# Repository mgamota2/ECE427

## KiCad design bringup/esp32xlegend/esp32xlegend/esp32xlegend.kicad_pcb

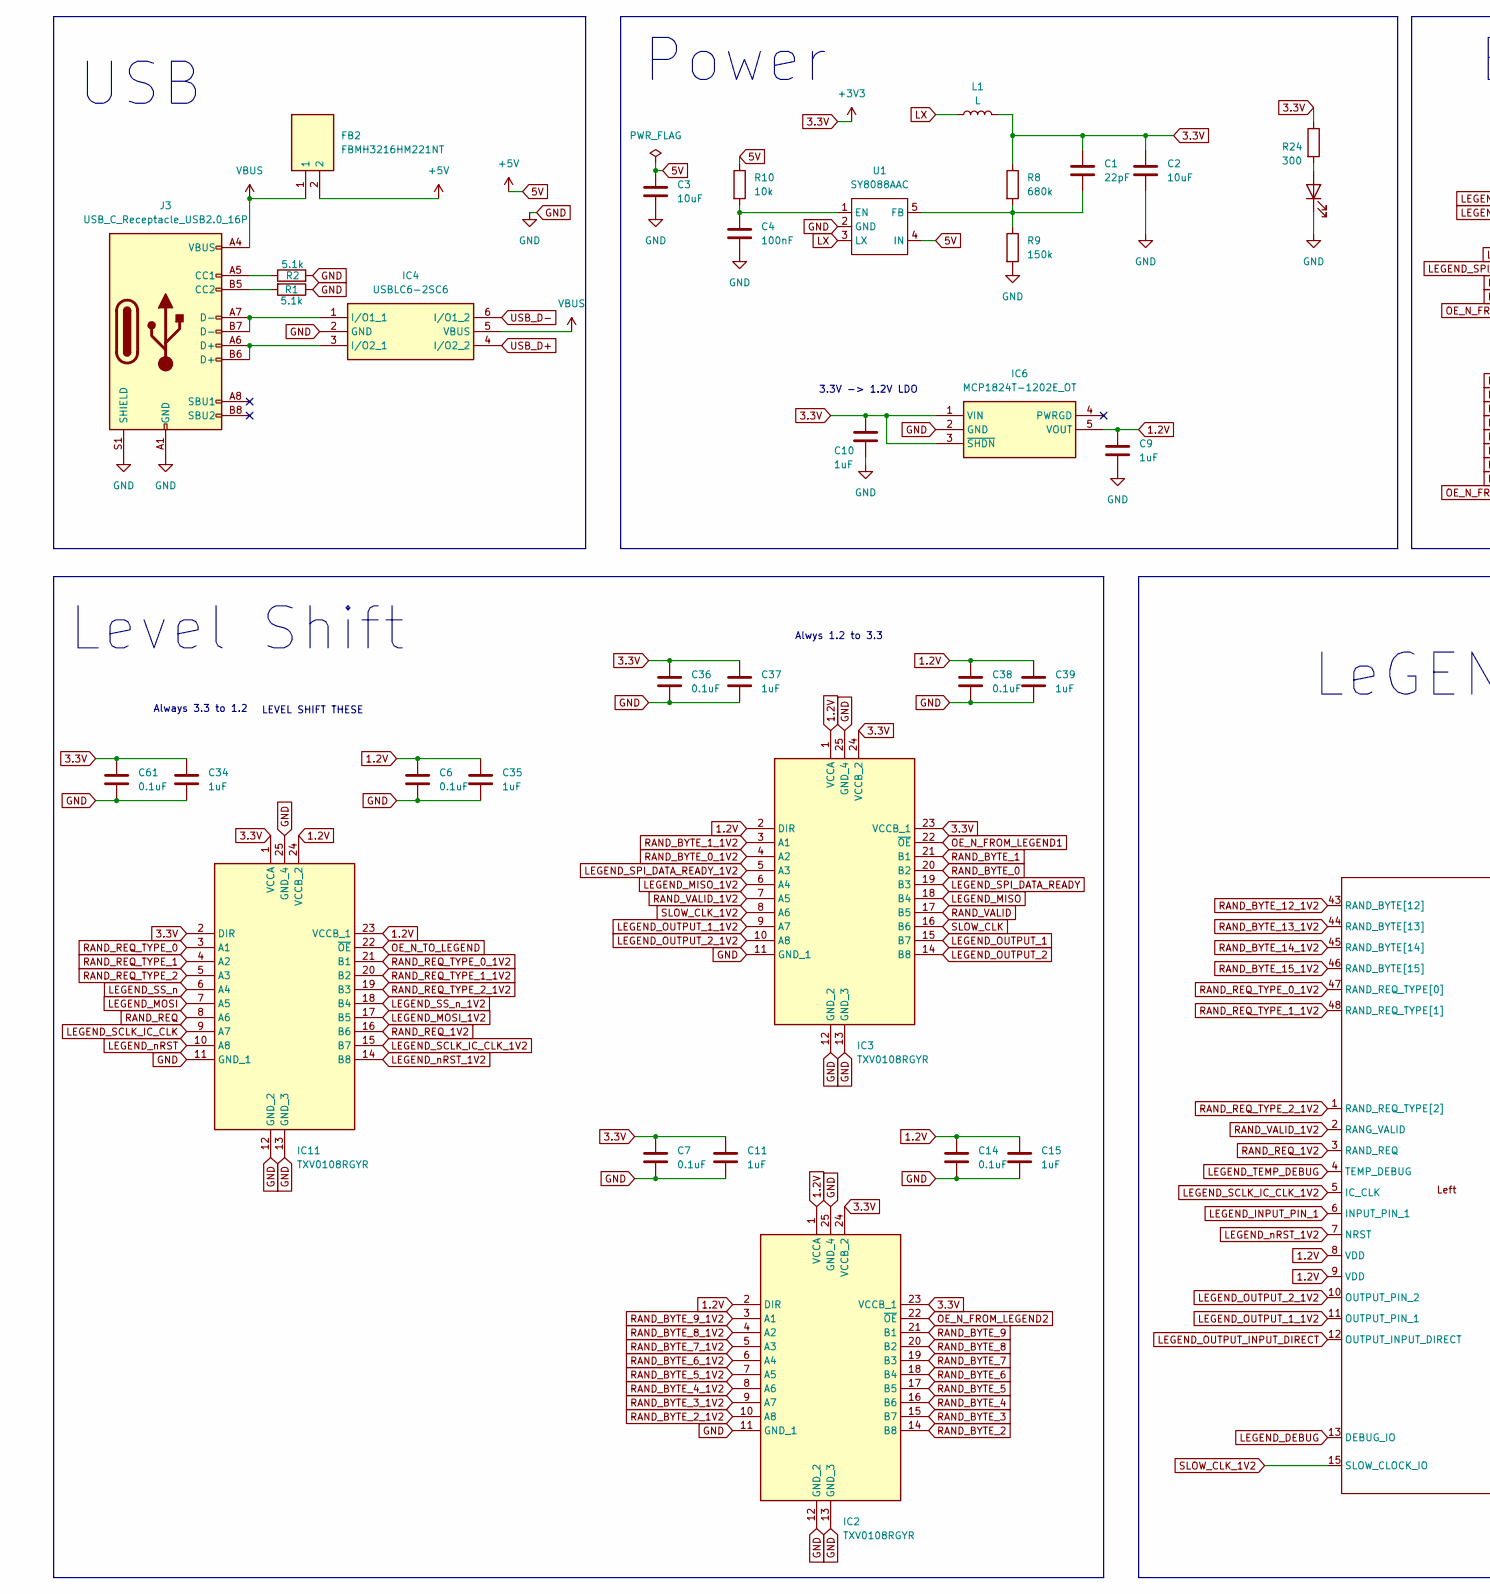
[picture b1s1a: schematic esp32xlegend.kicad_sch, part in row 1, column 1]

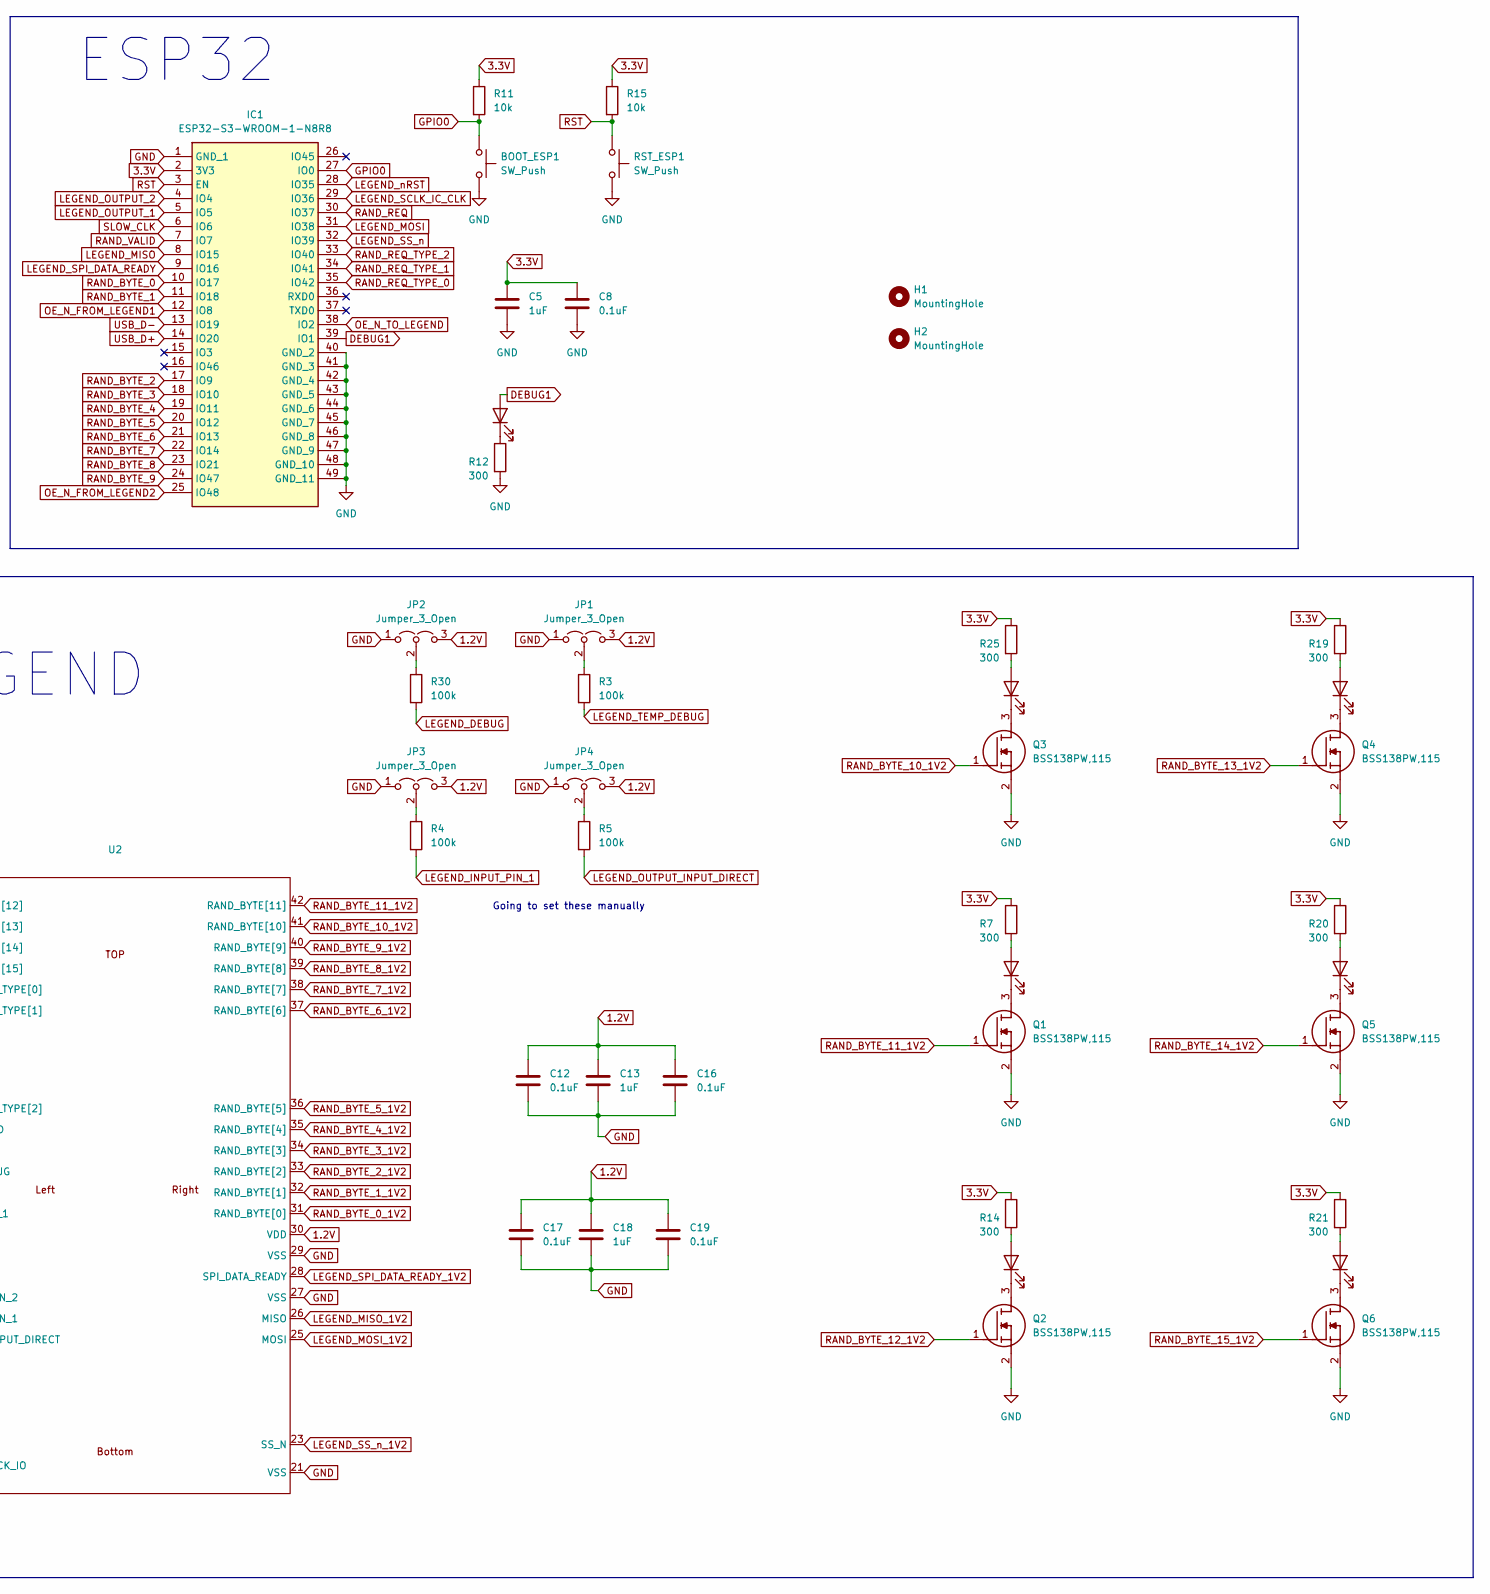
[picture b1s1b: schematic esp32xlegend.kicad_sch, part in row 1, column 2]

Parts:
3V3_1: LED; LED_0603_1608Metric
BOOT_ESP1: SW_Push; B3U1000PM
C1: 22pF; C_0603_1608Metric
C2, C3: 10uF; C_0603_1608Metric
C4: 100nF; C_0402_1005Metric
C5, C13, C18: 1uF; C_0603_1608Metric
C6, C7, C14, C36, C38, C61: 0.1uF; C_0402_1005Metric
C8, C12, C16, C17, C19: 0.1uF; C_0603_1608Metric
C9, C10, C11, C15, C34, C35, C37, C39: 1uF; C_0402_1005Metric
DEBUG3: LED; LED_0603_1608Metric
FB2: FBMH3216HM221NT; BEADC3216X180N; Mouser Part Number 963-FBMH3216HM221NT
H1, H2: MountingHole; MountingHole_2.2mm_M2
IC1: ESP32-S3-WROOM-1-N8R8; ESP32S3WROOM1N8R8; Mouser Part Number 356-EP32S3WROOM1N8R8
IC2, IC3, IC11: TXV0108RGYR; Mouser Part Number 595-TXV0108RGYR
IC4: USBLC6-2SC6; SOT95P280X145-6N; Mouser Part Number 511-USBLC6-2SC6
IC6: MCP1824T-1202E_OT; SOT95P270X145-5N; Mouser Part Number 579-MCP1824T-1202EOT
J3: USB_C_Receptacle_USB2.0_16P; USB_C_Receptacle_GCT_USB4085
JP1, JP2, JP3, JP4: Jumper_3_Open; SolderJumper-3_P1.3mm_Open_Pad1.0x1.5mm
L1: L; L_1008_2520Metric
Q1, Q2, Q3, Q4, Q5, Q6: BSS138PW,115; SOT65P210X110-3N; Mouser Part Number 771-BSS138PW115
R1, R2: 5.1k; R_0402_1005Metric
R3, R4, R5, R30: 100k; R_0402_1005Metric
R7, R12, R14, R19, R20, R21, R24, R25: 300; R_0402_1005Metric
R8: 680k; R_0603_1608Metric
R9: 150k; R_0603_1608Metric
R10: 10k; R_0603_1608Metric
R11, R15: 10k; R_0402_1005Metric
RAND10, RAND11, RAND12, RAND13, RAND14, RAND15: LED; LED_0603_1608Metric
RST_ESP1: SW_Push; B3U1000PM
U1: SY8088AAC; SOT-23-5_HandSoldering
U2: CHIP

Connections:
1.2V: C6.1, C9.1, C12.1, C13.1, C14.1, C15.1, C16.1, C17.1, C18.1, C19.1, C35.1, C38.1, C39.1, IC2.1 (VCCA), IC2.2 (DIR), IC3.1 (VCCA), IC3.2 (DIR), IC6.5 (VOUT), IC11.23 (VCCB_1), IC11.24 (VCCB_2), JP1.3 (B), JP2.3 (B), JP3.3 (B), JP4.3 (B), U2.8 (VDD), U2.9 (VDD), U2.30 (VDD)
3.3V: C1.1, C2.1, C5.1, C7.1, C8.1, C10.1, C11.1, C34.1, C36.1, C37.1, C61.1, IC1.2 (3V3), IC2.23 (VCCB_1), IC2.24 (VCCB_2), IC3.23 (VCCB_1), IC3.24 (VCCB_2), IC6.1 (VIN), IC6.3 (~SHDN), IC11.1 (VCCA), IC11.2 (DIR), L1.2, R7.1, R8.1, R11.1, R14.1, R15.1, R19.1, R20.1, R21.1, R24.1, R25.1
5V: C3.1, FB2.2, R10.1, U1.4 (IN)
DEBUG1: DEBUG3.2 (A), IC1.39 (IO1)
GND: 3V3_1.1 (K), BOOT_ESP1.2, C2.2, C3.2, C4.2, C5.2, C6.2, C7.2, C8.2, C9.2, C10.2, C11.2, C12.2, C13.2, C14.2, C15.2, C16.2, C17.2, C18.2, C19.2, C34.2, C35.2, C36.2, C37.2, C38.2, C39.2, C61.2, IC1.1 (GND_1), IC1.40 (GND_2), IC1.41 (GND_3), IC1.42 (GND_4), IC1.43 (GND_5), IC1.44 (GND_6), IC1.45 (GND_7), IC1.46 (GND_8), IC1.47 (GND_9), IC1.48 (GND_10), IC1.49 (GND_11), IC2.11 (GND_1), IC2.12 (GND_2), IC2.13 (GND_3), IC2.25 (GND_4), IC3.11 (GND_1), IC3.12 (GND_2), IC3.13 (GND_3), IC3.25 (GND_4), IC4.2 (GND), IC6.2 (GND), IC11.11 (GND_1), IC11.12 (GND_2), IC11.13 (GND_3), IC11.25 (GND_4), J3.A1 (GND), J3.A12 (GND), J3.B1 (GND), J3.B12 (GND), J3.S1 (SHIELD), JP1.1 (A), JP2.1 (A), JP3.1 (A), JP4.1 (A), Q1.2 (S), Q2.2 (S), Q3.2 (S), Q4.2 (S), Q5.2 (S), Q6.2 (S), R1.1, R2.2, R9.2, R12.2, RST_ESP1.2, U1.2 (GND), U2.21 (VSS), U2.27 (VSS), U2.29 (VSS)
GPIO0: BOOT_ESP1.1, IC1.27 (IO0), R11.2
LEGEND_DEBUG: R30.2, U2.13 (DEBUG_IO)
LEGEND_INPUT_PIN_1: R4.2, U2.6 (INPUT_PIN_1)
LEGEND_MISO: IC1.8 (IO15), IC3.18 (B4)
LEGEND_MISO_1V2: IC3.6 (A4), U2.26 (MISO)
LEGEND_MOSI: IC1.31 (IO38), IC11.7 (A5)
LEGEND_MOSI_1V2: IC11.17 (B5), U2.25 (MOSI)
LEGEND_OUTPUT_1: IC1.5 (IO5), IC3.15 (B7)
LEGEND_OUTPUT_1_1V2: IC3.9 (A7), U2.11 (OUTPUT_PIN_1)
LEGEND_OUTPUT_2: IC1.4 (IO4), IC3.14 (B8)
LEGEND_OUTPUT_2_1V2: IC3.10 (A8), U2.10 (OUTPUT_PIN_2)
LEGEND_OUTPUT_INPUT_DIRECT: R5.2, U2.12 (OUTPUT_INPUT_DIRECT)
LEGEND_SCLK_IC_CLK: IC1.29 (IO36), IC11.9 (A7)
LEGEND_SCLK_IC_CLK_1V2: IC11.15 (B7), U2.5 (IC_CLK)
LEGEND_SPI_DATA_READY: IC1.9 (IO16), IC3.19 (B3)
LEGEND_SPI_DATA_READY_1V2: IC3.5 (A3), U2.28 (SPI_DATA_READY)
LEGEND_SS_n: IC1.32 (IO39), IC11.6 (A4)
LEGEND_SS_n_1V2: IC11.18 (B4), U2.23 (SS_N)
LEGEND_TEMP_DEBUG: R3.2, U2.4 (TEMP_DEBUG)
LEGEND_nRST: IC1.28 (IO35), IC11.10 (A8)
LEGEND_nRST_1V2: IC11.14 (B8), U2.7 (NRST)
LX: L1.1, U1.3 (LX)
unnamed: 3V3_1.2 (A), R24.2
unnamed: DEBUG3.1 (K), R12.1
unnamed: IC4.1 (I/O1_1), J3.A7 (D-), J3.B7 (D-)
unnamed: IC4.3 (I/O2_1), J3.A6 (D+), J3.B6 (D+)
unnamed: J3.A5 (CC1), R2.1
unnamed: J3.B5 (CC2), R1.2
unnamed: JP1.2 (C), R3.1
unnamed: JP2.2 (C), R30.1
unnamed: JP3.2 (C), R4.1
unnamed: JP4.2 (C), R5.1
unnamed: Q1.3 (D), RAND11.1 (K)
unnamed: Q2.3 (D), RAND12.1 (K)
unnamed: Q3.3 (D), RAND10.1 (K)
unnamed: Q4.3 (D), RAND13.1 (K)
unnamed: Q5.3 (D), RAND14.1 (K)
unnamed: Q6.3 (D), RAND15.1 (K)
unnamed: R25.2, RAND10.2 (A)
unnamed: R7.2, RAND11.2 (A)
unnamed: R14.2, RAND12.2 (A)
unnamed: R19.2, RAND13.2 (A)
unnamed: R20.2, RAND14.2 (A)
unnamed: R21.2, RAND15.2 (A)
unnamed: C4.1, R10.2, U1.1 (EN)
unnamed: C1.2, R8.2, R9.1, U1.5 (FB)
OE_N_FROM_LEGEND1: IC1.12 (IO8), IC3.22 (~OE)
OE_N_FROM_LEGEND2: IC1.25 (IO48), IC2.22 (~OE)
OE_N_TO_LEGEND: IC1.38 (IO2), IC11.22 (~OE)
RAND_BYTE_0: IC1.10 (IO17), IC3.20 (B2)
RAND_BYTE_0_1V2: IC3.4 (A2), U2.31 (RAND_BYTE[0])
RAND_BYTE_1: IC1.11 (IO18), IC3.21 (B1)
RAND_BYTE_1_1V2: IC3.3 (A1), U2.32 (RAND_BYTE[1])
RAND_BYTE_2: IC1.17 (IO9), IC2.14 (B8)
RAND_BYTE_2_1V2: IC2.10 (A8), U2.33 (RAND_BYTE[2])
RAND_BYTE_3: IC1.18 (IO10), IC2.15 (B7)
RAND_BYTE_3_1V2: IC2.9 (A7), U2.34 (RAND_BYTE[3])
RAND_BYTE_4: IC1.19 (IO11), IC2.16 (B6)
RAND_BYTE_4_1V2: IC2.8 (A6), U2.35 (RAND_BYTE[4])
RAND_BYTE_5: IC1.20 (IO12), IC2.17 (B5)
RAND_BYTE_5_1V2: IC2.7 (A5), U2.36 (RAND_BYTE[5])
RAND_BYTE_6: IC1.21 (IO13), IC2.18 (B4)
RAND_BYTE_6_1V2: IC2.6 (A4), U2.37 (RAND_BYTE[6])
RAND_BYTE_7: IC1.22 (IO14), IC2.19 (B3)
RAND_BYTE_7_1V2: IC2.5 (A3), U2.38 (RAND_BYTE[7])
RAND_BYTE_8: IC1.23 (IO21), IC2.20 (B2)
RAND_BYTE_8_1V2: IC2.4 (A2), U2.39 (RAND_BYTE[8])
RAND_BYTE_9: IC1.24 (IO47), IC2.21 (B1)
RAND_BYTE_9_1V2: IC2.3 (A1), U2.40 (RAND_BYTE[9])
RAND_BYTE_10_1V2: Q3.1 (G), U2.41 (RAND_BYTE[10])
RAND_BYTE_11_1V2: Q1.1 (G), U2.42 (RAND_BYTE[11])
RAND_BYTE_12_1V2: Q2.1 (G), U2.43 (RAND_BYTE[12])
RAND_BYTE_13_1V2: Q4.1 (G), U2.44 (RAND_BYTE[13])
RAND_BYTE_14_1V2: Q5.1 (G), U2.45 (RAND_BYTE[14])
RAND_BYTE_15_1V2: Q6.1 (G), U2.46 (RAND_BYTE[15])
RAND_REQ: IC1.30 (IO37), IC11.8 (A6)
RAND_REQ_1V2: IC11.16 (B6), U2.3 (RAND_REQ)
RAND_REQ_TYPE_0: IC1.35 (IO42), IC11.3 (A1)
RAND_REQ_TYPE_0_1V2: IC11.21 (B1), U2.47 (RAND_REQ_TYPE[0])
RAND_REQ_TYPE_1: IC1.34 (IO41), IC11.4 (A2)
RAND_REQ_TYPE_1_1V2: IC11.20 (B2), U2.48 (RAND_REQ_TYPE[1])
RAND_REQ_TYPE_2: IC1.33 (IO40), IC11.5 (A3)
RAND_REQ_TYPE_2_1V2: IC11.19 (B3), U2.1 (RAND_REQ_TYPE[2])
RAND_VALID: IC1.7 (IO7), IC3.17 (B5)
RAND_VALID_1V2: IC3.7 (A5), U2.2 (RANG_VALID)
RST: IC1.3 (EN), R15.2, RST_ESP1.1
SLOW_CLK: IC1.6 (IO6), IC3.16 (B6)
SLOW_CLK_1V2: IC3.8 (A6), U2.15 (SLOW_CLOCK_IO)
USB_D+: IC1.14 (IO20), IC4.4 (I/O2_2)
USB_D-: IC1.13 (IO19), IC4.6 (I/O1_2)
VBUS: FB2.1, IC4.5 (VBUS), J3.A4 (VBUS), J3.A9 (VBUS), J3.B4 (VBUS), J3.B9 (VBUS)

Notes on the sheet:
3.3V -> 1.2V LDO
Power
ESP32
LEVEL SHIFT THESE
Level Shift
Going to set these manually
USB
Alwys 1.2 to 3.3
Always 3.3 to 1.2
LeGEND

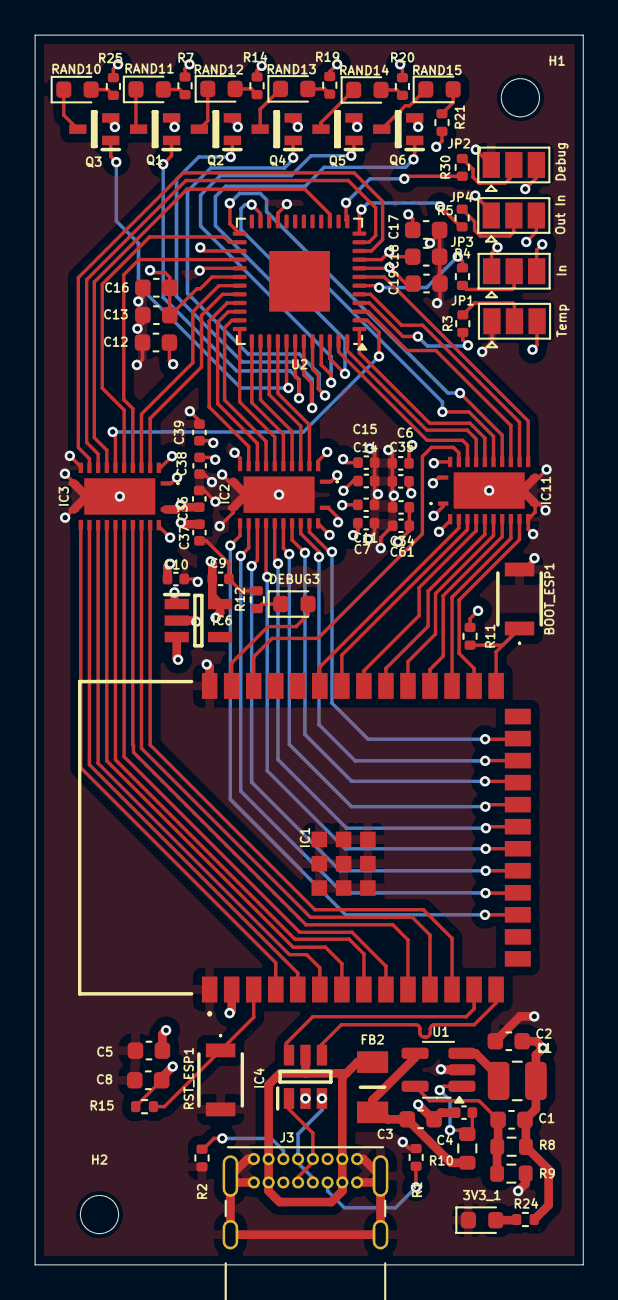
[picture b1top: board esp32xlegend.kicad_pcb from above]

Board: 4 copper layers, 31.6 x 70.9 mm, 78 parts (0 on the bottom side), 96 nets.

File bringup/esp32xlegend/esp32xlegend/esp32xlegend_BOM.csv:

Reference,Value,Datasheet,Footprint,Qty,DNP,JLCPCB #
"3V3_1,DEBUG3,RAND10,RAND11,RAND12,RAND13,RAND14,RAND15",LED,~,LED_SMD:LED_0603_1608Metric,8,,C72041
"BOOT_ESP1,RST_ESP1",SW_Push,~,SamacSys_Parts:B3U1000PM,2,,C231329
C1,22pF,~,Capacitor_SMD:C_0603_1608Metric,1,,C1653
"C2,C3",10uF,~,Capacitor_SMD:C_0603_1608Metric,2,,C1691
C4,100nF,~,Capacitor_SMD:C_0402_1005Metric,1,,C1525
"C5,C13,C18",1uF,~,Capacitor_SMD:C_0603_1608Metric,3,,C1592
"C6,C7,C14,C36,C38,C61",0.1uF,~,Capacitor_SMD:C_0402_1005Metric,6,,C1525
"C8,C12,C16,C17,C19",0.1uF,~,Capacitor_SMD:C_0603_1608Metric,5,,C1590
"C9,C10,C11,C15,C34,C35,C37,C39",1uF,~,Capacitor_SMD:C_0402_1005Metric,8,,C14445
FB2,FBMH3216HM221NT,https://ds.yuden.co.jp/TYCOMPAS/ut/detail?pn=FBMH3216HM221NT &u=M,SamacSys_Parts:BEADC3216X180N,1,,C7217634
IC1,ESP32-S3-WROOM-1-N8R8,https://www.espressif.com/sites/default/files/documentation/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,SamacSys_Parts:ESP32S3WROOM1N8R8,1,,C2913201
"IC2,IC3,IC11",TXV0108RGYR,https://www.ti.com/lit/ds/symlink/txv0108.pdf?ts=17104185317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,SamacSys_Parts:TXV0108RGYR,3,,C22428389
IC4,USBLC6-2SC6,http://www.st.com/st-web-ui/static/active/en/resource/techni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,SamacSys_Parts:SOT95P280X145-6N,1,,C7519
IC6,MCP1824T-1202E_OT,https://ww1.microchip.com/downloads/en/DeviceDoc/22070a.pdf,SamacSys_Parts:SOT95P270X145-5N,1,,C625461
J3,USB_C_Receptacle_USB2.0_16P,https://www.usb.org/sites/default/files/documents/usb_type-c.zip,Connector_USB:USB_C_Receptacle_GCT_USB4085,1,,C36936564
L1,L,~,Inductor_SMD:L_1008_2520Metric,1,,C23894
"Q1,Q2,Q3,Q4,Q5,Q6","BSS138PW,115",https://assets.nexperia.com/documents/data-sheet/BSS138PW.pdf,SamacSys_Parts:SOT65P210X110-3N,6,,C193366
"R1,R2",5.1k,~,Resistor_SMD:R_0402_1005Metric,2,,C25905
"R3,R4,R5,R30",100k,~,Resistor_SMD:R_0402_1005Metric,4,,C25530
"R7,R12,R14,R19,R20,R21,R24,R25",300,~,Resistor_SMD:R_0402_1005Metric,8,,C25102
R8,680k,~,Resistor_SMD:R_0603_1608Metric,1,,C25822
R9,150k,~,Resistor_SMD:R_0603_1608Metric,1,,C22807
R10,10k,~,Resistor_SMD:R_0603_1608Metric,1,,C15401
"R11,R15",10k,~,Resistor_SMD:R_0402_1005Metric,2,,C25531
U1,SY8088AAC,,Package_TO_SOT_SMD:SOT-23-5_HandSoldering,1,,C79313
U2,~,,LEGEND:CHIP,1,DNP,

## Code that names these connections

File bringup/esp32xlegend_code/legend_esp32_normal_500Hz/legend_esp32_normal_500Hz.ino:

// LEGEND is a custom random number generator ASIC. It has a debug mode and a default mode. In debug
// mode, the user can test submodules and route external inputs (INPUT pin) to intermediate submodules and route
// internal signals to the OUTPUT1 and OUTPUT 2 pins. In default mode, the RAND_REQ_TYPE pins are configured
// to request a 16, 32, or 64 bit RDSEED or RDRAND. Rand req must go high to submit the request. The output is
// sampled from the RAND_BYTE [0:15] pins, only [0:9] is sent to the ESP32 S3 WROOM. LEGEND operates at 1.2V
// so level shifters are used for all inputs and outputs. These level shifters are enabled with "OE_N_TO_LEGEND", 
// "OE_N_FROM_LEGEND1" and "OE_N_FROM_LEGEND2". Output bits in default mode are sampled when RAND_VALID is high
// and the bits are updated on the rising edge of SLOW_CLK.
// In debug mode, the CLK pin is used as the SPI clock to interface with a custom 22-bit message SPI interface. 
// All commands are register reads or writes, but write commands that write to the "debug state register" are treated
// specially as "Mux configuration commands". These commands select which submodules the output and input pins connect to.

#define LEGEND_OUTPUT_2 4
#define LEGEND_OUTPUT_1 5
#define LEGEND_SLOW_CLK 6
#define RAND_VALID 7
#define LEGEND_MISO 15
#define LEGEND_SPI_DATA_READY 16
#define RAND_BYTE_0 17
#define RAND_BYTE_1 18
#define OE_N_FROM_LEGEND_1 8
#define RAND_BYTE_2 9
#define RAND_BYTE_3 10
#define RAND_BYTE_4 11
#define RAND_BYTE_5 12
#define RAND_BYTE_6 13
#define RAND_BYTE_7 14
#define RAND_BYTE_8 21
#define RAND_BYTE_9 47
#define OE_N_FROM_LEGEND_2 48
#define LEGEND_nRST 35
#define LEGEND_SCLK_IC_CLK 36
#define RAND_REQ 37
#define LEGEND_MOSI 38
#define LEGEND_SS_n 39
#define RAND_REQ_TYPE_2 40
#define RAND_REQ_TYPE_1 41
#define RAND_REQ_TYPE_0 42
#define OE_N_TO_LEGEND 2
#define DEBUG1 1

#define HALF_PERIOD     1   // 1 ms half period -> 500 Hz clock
#define RESET_HOLD_MS   10
#define RESET_SETTLE_MS 10

#define SLOW_CLK_PERIOD_MS  (HALF_PERIOD * 2 * 2)
#define REPORT_INTERVAL_MS  ((RING_BUF_SIZE - 1) * SLOW_CLK_PERIOD_MS)


// --- Ring buffer for captured samples ---
#define RING_BUF_SIZE 64

struct RandSample {
    uint16_t rand_bits;   // RAND_BYTE[9:0], 10 bits
    uint32_t timestamp_ms;
};

RandSample ring_buf[RING_BUF_SIZE];
volatile uint16_t ring_head = 0;  // next write index
volatile uint16_t ring_count = 0; // how many valid entries

// Parallel array of RAND_BYTE pins in bit order [0..9]
const int RAND_PINS[10] = {
    RAND_BYTE_0, RAND_BYTE_1, RAND_BYTE_2, RAND_BYTE_3,
    RAND_BYTE_4, RAND_BYTE_5, RAND_BYTE_6, RAND_BYTE_7,
    RAND_BYTE_8, RAND_BYTE_9
};

// Read all 10 RAND_BYTE pins and pack into a uint16_t (bit 0 = RAND_BYTE_0)
uint16_t read_rand_bits() {
    uint16_t val = 0;
    for (int i = 0; i < 10; i++) {
        if (digitalRead(RAND_PINS[i])) {
            val |= (1u << i);
        }
    }
    return val;
}

// Push a sample into the ring buffer
void push_sample(uint16_t bits) {
    ring_buf[ring_head].rand_bits    = bits;
    ring_buf[ring_head].timestamp_ms = millis();
    ring_head = (ring_head + 1) % RING_BUF_SIZE;
    if (ring_count < RING_BUF_SIZE) ring_count++;
}

// Drain and print all buffered samples over Serial
void flush_samples() {
    if (ring_count == 0) return;

    // Walk from oldest to newest
    uint16_t oldest = (ring_head - ring_count + RING_BUF_SIZE) % RING_BUF_SIZE;
    for (uint16_t i = 0; i < ring_count; i++) {
        uint16_t idx = (oldest + i) % RING_BUF_SIZE;
        RandSample &s = ring_buf[idx];
        Serial.printf("[%8lu ms] RAND_BYTE[9:0] = 0x%03X  (%04u decimal)  0b",
                      s.timestamp_ms, s.rand_bits, s.rand_bits);
        // Print binary MSB first
        for (int b = 9; b >= 0; b--) {
            Serial.print((s.rand_bits >> b) & 1);
        }
        Serial.println();
    }
    ring_count = 0;
    ring_head  = 0;
}

void setup() {
    Serial.begin(115200);

    // --- Enable level shifters ---
    pinMode(OE_N_TO_LEGEND, OUTPUT);
    digitalWrite(OE_N_TO_LEGEND, LOW);

    pinMode(OE_N_FROM_LEGEND_1, OUTPUT);
    digitalWrite(OE_N_FROM_LEGEND_1, LOW);

    pinMode(OE_N_FROM_LEGEND_2, OUTPUT);
    digitalWrite(OE_N_FROM_LEGEND_2, LOW);

    // --- Default mode control pins ---
    pinMode(RAND_REQ_TYPE_2, OUTPUT); digitalWrite(RAND_REQ_TYPE_2, LOW);
    pinMode(RAND_REQ_TYPE_1, OUTPUT); digitalWrite(RAND_REQ_TYPE_1, HIGH);
    pinMode(RAND_REQ_TYPE_0, OUTPUT); digitalWrite(RAND_REQ_TYPE_0, LOW);
    pinMode(RAND_REQ, OUTPUT);        digitalWrite(RAND_REQ, HIGH);

    pinMode(LEGEND_SCLK_IC_CLK, OUTPUT); digitalWrite(LEGEND_SCLK_IC_CLK, LOW);
    pinMode(DEBUG1, OUTPUT);             digitalWrite(DEBUG1, LOW);

    // --- SPI idle ---
    pinMode(LEGEND_SS_n, OUTPUT);  digitalWrite(LEGEND_SS_n, HIGH);
    pinMode(LEGEND_MOSI, OUTPUT);  digitalWrite(LEGEND_MOSI, LOW);

    // --- LEGEND outputs: inputs to ESP32 ---
    pinMode(LEGEND_SLOW_CLK, INPUT_PULLDOWN);
    pinMode(RAND_VALID,       INPUT_PULLDOWN);
    for (int i = 0; i < 10; i++) {
        pinMode(RAND_PINS[i], INPUT_PULLDOWN);
    }
    // Unused LEGEND outputs — still configure to avoid floating
    pinMode(LEGEND_OUTPUT_1,        INPUT_PULLDOWN);
    pinMode(LEGEND_OUTPUT_2,        INPUT_PULLDOWN);
    pinMode(LEGEND_MISO,            INPUT_PULLDOWN);
    pinMode(LEGEND_SPI_DATA_READY,  INPUT_PULLDOWN);

    // --- Reset sequence ---
    pinMode(LEGEND_nRST, OUTPUT);
    digitalWrite(LEGEND_nRST, LOW);
    delay(RESET_HOLD_MS);
    digitalWrite(LEGEND_nRST, HIGH);
    delay(RESET_SETTLE_MS);

    Serial.println("LEGEND running — sampling RAND_BYTE[9:0] on SLOW_CLK rising edge when RAND_VALID=1");
}

// Track previous SLOW_CLK state for edge detection
bool clk_prev = false;

// Accumulate edges between Serial prints
uint32_t total_clk_edges  = 0;
uint32_t total_valid_samples = 0;
uint32_t last_report_ms   = 0;

void loop() {
    // --- Drive ESP32 clock and mirror to LED ---
    digitalWrite(LEGEND_SCLK_IC_CLK, HIGH);
    digitalWrite(DEBUG1, HIGH);
    delay(HALF_PERIOD);

    digitalWrite(LEGEND_SCLK_IC_CLK, LOW);
    digitalWrite(DEBUG1, LOW);
    delay(HALF_PERIOD);

    // --- Detect SLOW_CLK rising edge from LEGEND ---
    bool clk_now = digitalRead(LEGEND_SLOW_CLK);
    if (clk_now && !clk_prev) {
        // Rising edge — bits are now valid/updated per the datasheet
        total_clk_edges++;

        if (digitalRead(RAND_VALID)) {
            uint16_t bits = read_rand_bits();
            push_sample(bits);
            total_valid_samples++;
        }
    }
    clk_prev = clk_now;

    // --- Periodically flush buffered samples to Serial ---
    uint32_t now = millis();
    if (now - last_report_ms >= REPORT_INTERVAL_MS) {
        Serial.printf("--- CLK edges: %lu  |  valid samples: %lu ---\n",
                      total_clk_edges, total_valid_samples);
        flush_samples();
        last_report_ms = now;
    }
}

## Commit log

2026-02-28 Added report
2026-06-03 bringup
2026-06-03 media
